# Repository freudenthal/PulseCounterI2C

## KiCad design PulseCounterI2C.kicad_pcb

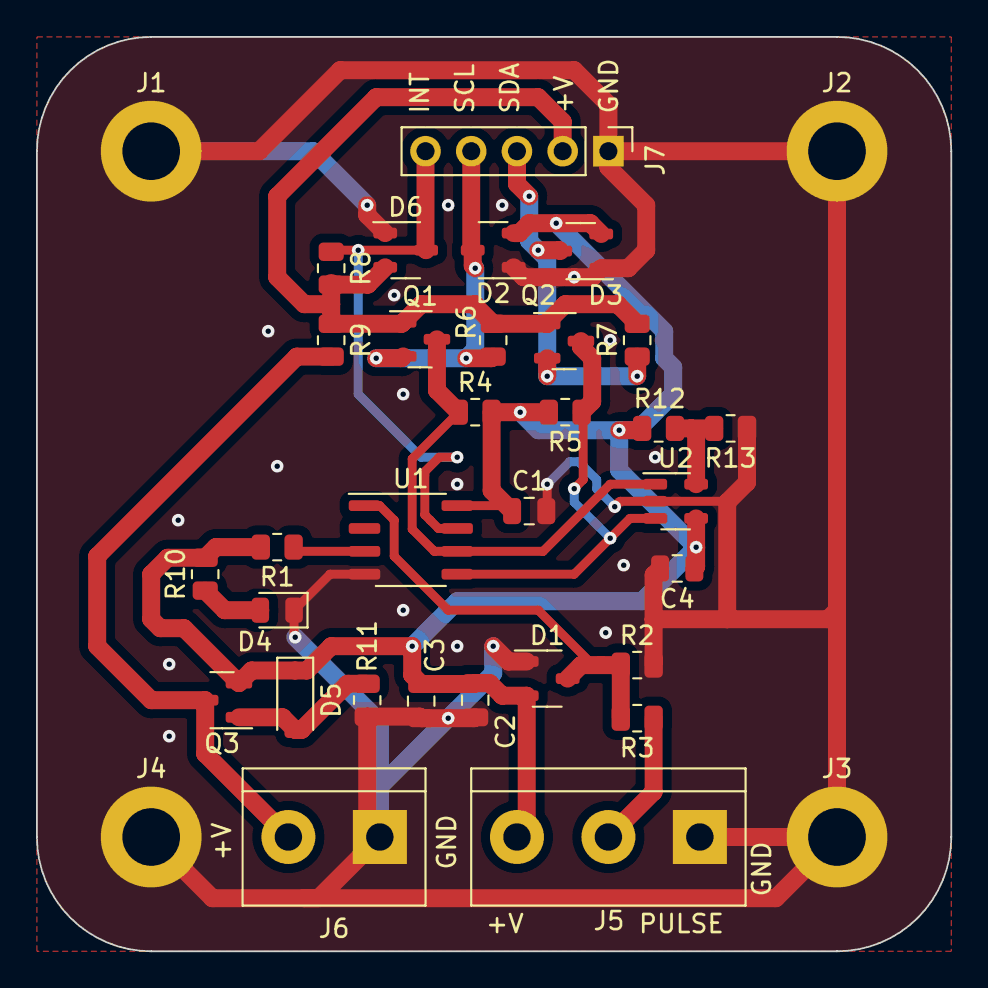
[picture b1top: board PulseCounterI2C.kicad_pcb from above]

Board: 2 copper layers, 50.8 x 50.8 mm, 35 parts (0 on the bottom side), 15 nets.

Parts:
C1, C2, C3, C4: 1uF; C_0805_2012Metric
D1, D2, D3, D6: 100V; SOT-23-3
D4: LED; LED_0805_2012Metric
D5: 10V; D_SOD-123
J1, J2, J3, J4: M3; MountingHole_3.2mm_M3_DIN965_Pad
J5: Pulse; TerminalBlock_bornier-3_P5.08mm
J6: 5Vin; TerminalBlock_bornier-2_P5.08mm
J7: I2C; PinHeader_1x05_P2.54mm_Vertical
Q1, Q2: Q_NMOS_GSD; SOT-23
Q3: Q_PMOS_GSD; SOT-23
R1, R2, R4, R5, R6, R7, R8, R12, R13: 10kΩ; R_0805_2012Metric
R3, R10: 500Ω; R_0805_2012Metric
R9: NS; R_0805_2012Metric
R11: 100kΩ; R_0805_2012Metric
U1: PCF8593; SO-8_3.9x4.9mm_P1.27mm
U2: 24FC01T-I/OT; SOT-23-5

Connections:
+5V: C1.1, C2.1, C3.1, C4.1, D1.2 (K), D2.2 (K), D3.2 (K), D5.1 (K), J5.3, Q3.2 (S), R1.2, R4.2, R5.2, R10.2, R12.2, U1.8 (V_{DD}), U2.4 (V_{CC})
/EEPROMI2C/SCL: Q1.3 (D), R4.1, U1.6 (SCL), U2.1 (SCL)
/EEPROMI2C/SDA: Q2.3 (D), R5.1, U1.5 (SDA), U2.3 (SDA)
/I2CConnector/INT: D6.3 (A), J7.5, R8.1, U1.7 (~INT)
/I2CConnector/VI2C: D6.2 (K), J7.2, Q1.1 (G), Q2.1 (G), R6.2, R7.2, R8.2, R9.1
/PCF8593/Pulse: D1.3 (A), R2.1, R3.2, U1.1 (OSCI)
GND: C1.2, C2.2, C3.2, C4.2, D1.1 (K), D2.1 (K), D3.1 (K), D4.1 (K), D6.1 (K), J1.1, J2.1, J3.1, J4.1, J5.1, J6.1, J7.1, R2.2, R11.1, R13.1, U1.4 (V_{SS}), U2.2 (GND)
unnamed: D2.3 (A), J7.4, Q1.2 (S), R6.1
unnamed: D3.3 (A), J7.3, Q2.2 (S), R7.1
unnamed: D4.2 (A), R10.1
unnamed: D5.2 (A), Q3.1 (G), R11.2
unnamed: J5.2, R3.1
unnamed: J6.2, Q3.3 (D), R9.2
unnamed: R1.1, U1.3 (~RESET)
unnamed: R12.1, R13.2, U2.5 (WP)
